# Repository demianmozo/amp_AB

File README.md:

# Amplificador de Audio Clase AB

Repositorio con los archivos de diseño, simulación y fabricación de un amplificador de audio Clase AB, desarrollado como proyecto final para la asignatura **Proyecto Transversal V** de la **Universidad Nacional de Mar del Plata (UNMDP)**.

## 👥 Equipo de Trabajo
* **Ian P. Larrieu Lacoste**
* **Augusto Loyza**
* **Demian N. Mozo**

## 📝 Descripción del proyecto
El sistema cuenta con las siguientes características principales:
* **Topología:** Amplificador de potencia de audio Clase AB (utilizando transistores Darlington TIP141/146).
* **PCB:** Diseño simple faz (ruteado en la capa inferior `B.Cu`) pensado para CNC.

## 🛠️ Herramientas utilizadas
* **LTspice:** Simulación eléctrica del circuito y análisis de respuesta en frecuencia.
* **KiCad (v10):** Captura de esquemático y diseño del Layout del PCB (generación de Gerbers y Drill files).

## ⚙️ Notas de fabricación (CNC)
⚠️ **IMPORTANTE:** Para fabricar este PCB en la CNC:

1. **Importar archivos:** Cargar los archivos de cobre (`amp_AB-B_Cu.gbr`), contorno (`amp_AB-Edge_Cuts.gbr`) y los archivos de perforación (`amp_AB-PTH.drl` y `amp_AB-NPTH.drl`).
2. **Espejado (Mirror):** Como el ruteo se diseñó visto desde la capa superior (Top), se deben **seleccionar todos los archivos importados** y espejarlos simultáneamente (respecto al eje X o Y) utilizando la herramienta de FlatCAM. 
3. **Isolation Routing:** Generar las pasadas de la fresa.
4. **Perforación y Corte (Cutout):** Generar los G-Codes correspondientes para los agujeros y el corte del perímetro (`Edge_Cuts`).

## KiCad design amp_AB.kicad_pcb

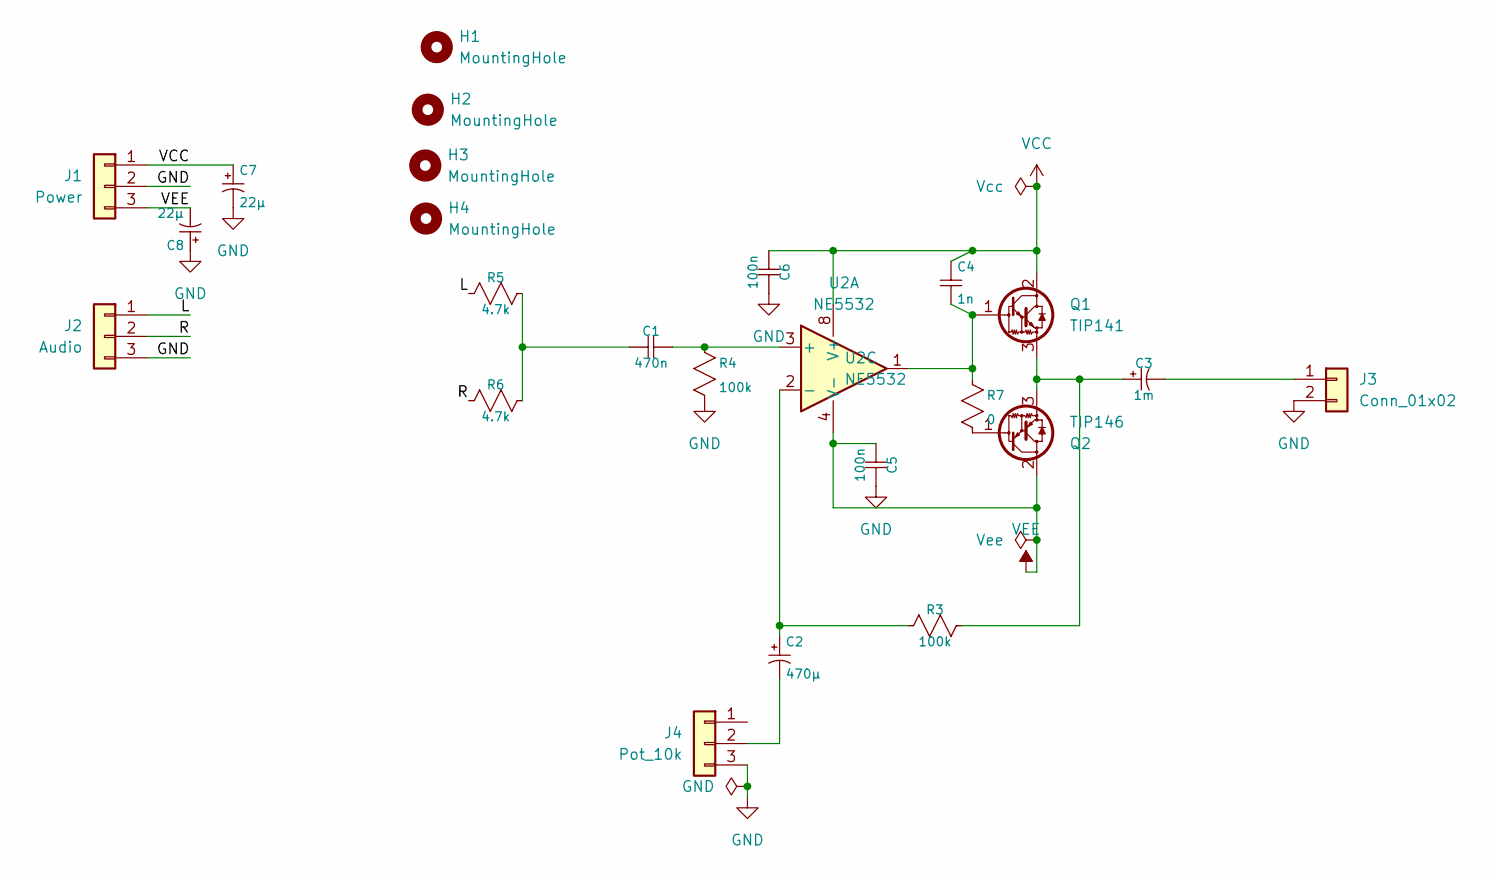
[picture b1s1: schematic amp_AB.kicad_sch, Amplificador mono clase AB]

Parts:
C1: 470n; C_Rect_L13.0mm_W6.0mm_P10.00mm_FKS3_FKP3_MKS4
C2: 470µ; CP_Radial_D8.0mm_P3.50mm
C3: 1m; CP_Radial_D10.0mm_P5.00mm
C4: 1n; C_Disc_D5.0mm_W2.5mm_P5.00mm
C5: 100n; C_Rect_L7.0mm_W3.5mm_P5.00mm
C6: 100n; C_Rect_L10.0mm_W4.0mm_P7.50mm_MKS4
C7, C8: 22µ; CP_Radial_D10.0mm_P5.00mm
H1, H2, H3, H4: MountingHole; MountingHole_3.2mm_M3
J1: Power; Molex_KK-254_AE-6410-03A_1x03_P2.54mm_Vertical
J2: Audio; Molex_KK-254_AE-6410-03A_1x03_P2.54mm_Vertical
J3: Conn_01x02; TerminalBlock_bornier-2_P5.08mm
J4: Pot_10k; Molex_KK-254_AE-6410-03A_1x03_P2.54mm_Vertical
Q1: TIP141; TO-218-3_Vertical
Q2: TIP146; TO-218-3_Vertical
R3, R4: 100k; R_Axial_DIN0207_L6.3mm_D2.5mm_P10.16mm_Horizontal
R5, R6: 4.7k; R_Axial_DIN0207_L6.3mm_D2.5mm_P10.16mm_Horizontal
R7: 0; R_Axial_DIN0207_L6.3mm_D2.5mm_P10.16mm_Horizontal
U2: NE5532; DIP-8_W7.62mm_Socket

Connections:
/L: J2.1, R5.2
/R: J2.2, R6.2
GND: C5.1, C6.1, C7.2 (B), C8.1 (A), J1.2, J2.3, J3.2, J4.3, R4.2
unnamed: C1.2, R5.1, R6.1
unnamed: C2.1 (A), R3.2, U2.2 (-)
unnamed: C2.2 (B), J4.2
unnamed: C3.1 (A), Q1.3 (E), Q2.3 (E), R3.1
unnamed: C3.2 (B), J3.1
unnamed: C4.2, Q1.1 (B), R7.1, U2.1
unnamed: Q2.1 (B), R7.2
unnamed: C1.1, R4.1, U2.3 (+)
VCC: C4.1, C6.2, C7.1 (A), J1.1, Q1.2 (C), U2.8 (V+)
VEE: C5.2, C8.2 (B), J1.3, Q2.2 (C), U2.4 (V-)

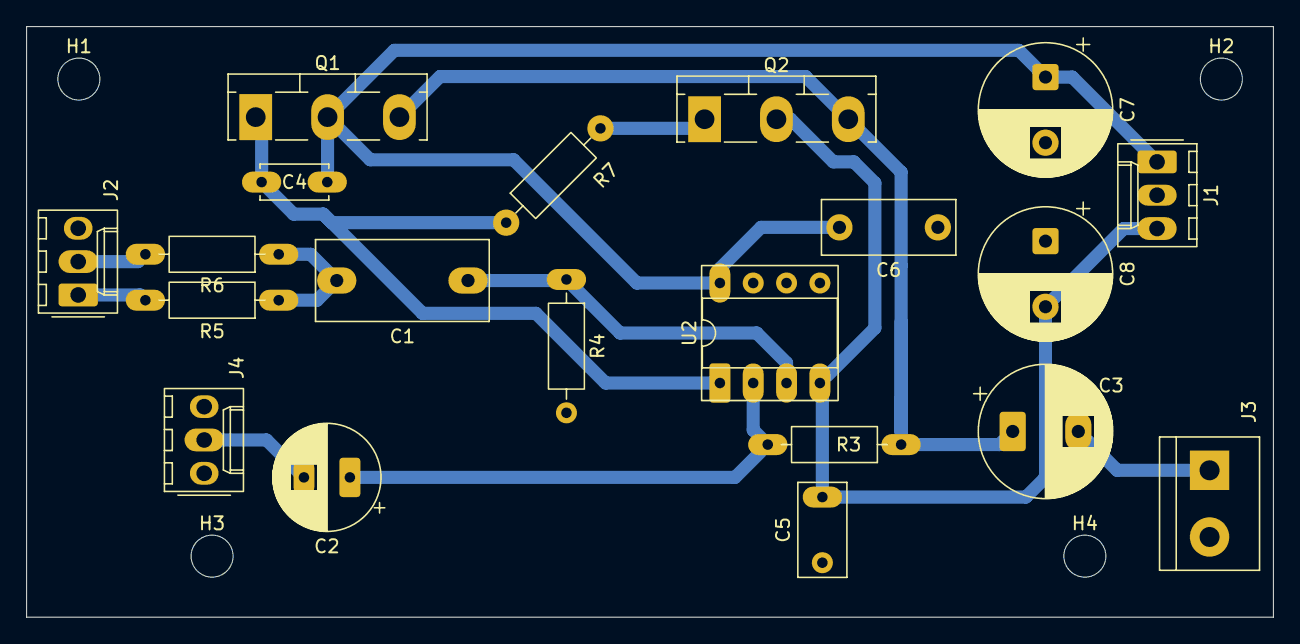
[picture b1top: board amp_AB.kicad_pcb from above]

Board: 2 copper layers, 95.0 x 45.0 mm, 24 parts (0 on the bottom side), 13 nets.

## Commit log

2026-06-16 EL HUEVO SAPE
2026-06-18 agregue los footprints faltantes. Esquematico terminado
2026-06-18 primer diseño de pcb
2026-06-21 Termine el routing y puse los mounting holes
2026-06-21 listo el pollo falta la carcasa
2026-06-21 Ultimos detalles y exportado de gerbers
2026-06-21 Update .gitignore to remove fabrication outputs
    Removed fabrication output files from .gitignore.
2026-06-21 gerbers
2026-06-22 caja huvistica
2026-06-22 Diseño de carcasa en /case
2026-06-22 Update .gitignore
    Added macOS specific files and compressed files to .gitignore.
2026-06-22 Lamina
2026-06-22 Caja y tapa listos
2026-06-22 Corregidas las islas desconectadas
